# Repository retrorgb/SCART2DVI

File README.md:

# SCART2DVI
Please refer to the [SCART2DVI](https://www.retrorgb.com/scart2dvi.html) page on RetroRGB for more information.

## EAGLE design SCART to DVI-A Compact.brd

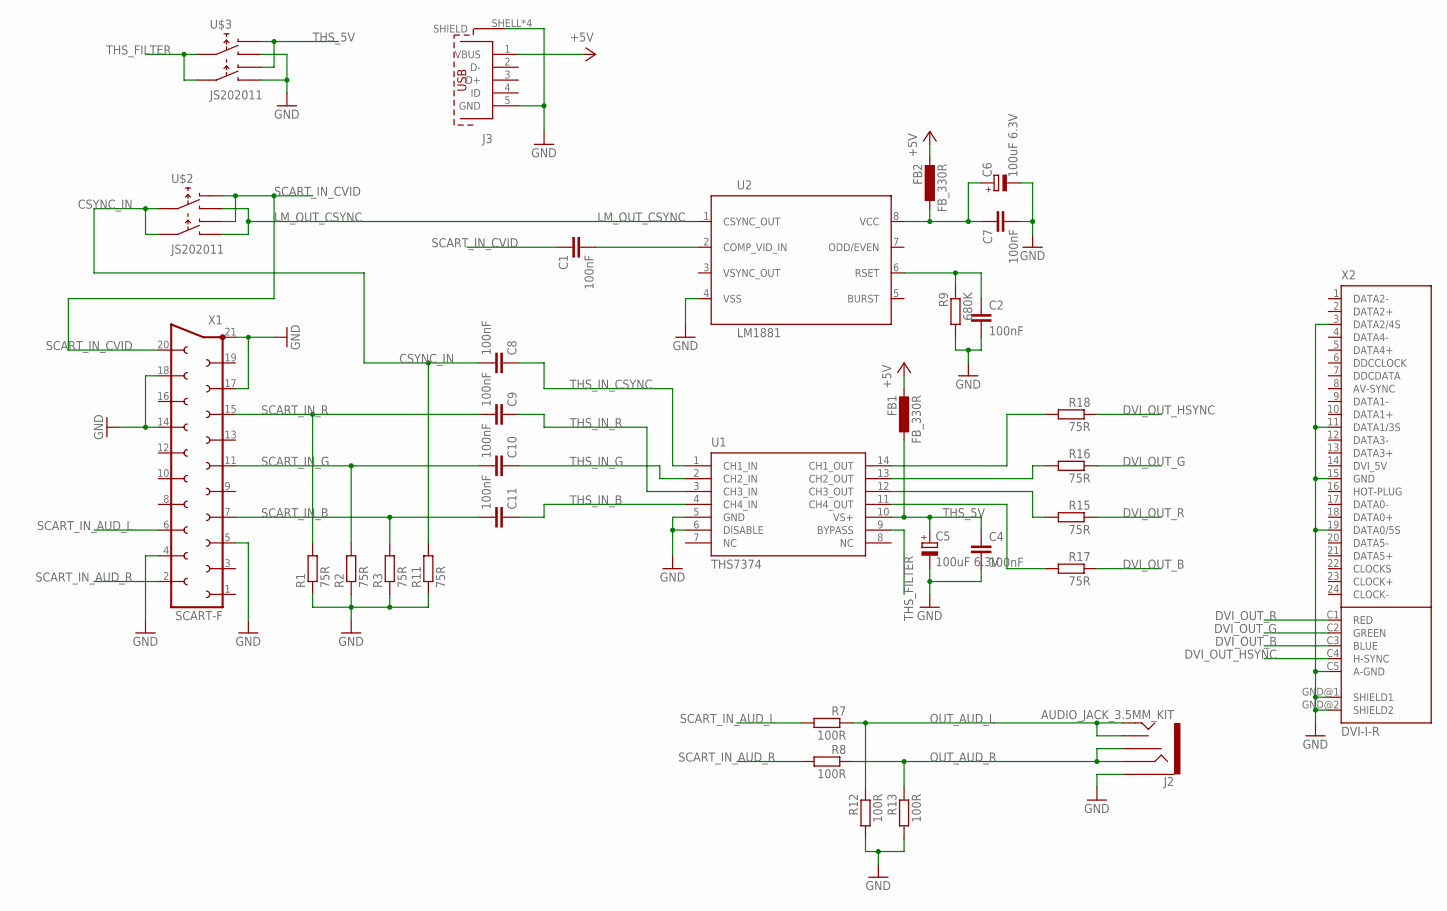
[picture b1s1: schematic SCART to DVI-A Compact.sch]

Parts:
C1, C2, C4, C7, C8, C9, C10, C11: 100nF; C0603
C5, C6: 100uF 6.3V; PANASONIC_B
FB1, FB2: FB_330R; L2012C
J2: AUDIO_JACK_3.5MM_KIT; AUDIO-JACK-KIT
J3: 629105150521
R1, R2, R3, R11, R15, R16, R17, R18: 75R; R0603
R7, R8, R12, R13: 100R; R0603
R9: 680K; R0603
U1: THS7374; SO14W
U2: LM1881; SO08
U$2, U$3: JS202011
X1: SCART-F
X2: DVI-I-R

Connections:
+5V: FB1.2, FB2.2, J3.1 (VBUS)
AGND: X2.C6 (AGND)
CH1_OUT: R15.2, U1.12 (CH3_OUT)
CH2_OUT: R16.2, U1.13 (CH2_OUT)
CH3_OUT: R17.2, U1.11 (CH4_OUT)
CH4_OUT: R18.2, U1.14 (CH1_OUT)
CSYNC_IN: C8.2, R11.2, U$2.2, U$2.5
DVI_5V: X2.14 (DVI_5V)
DVI_OUT_B: R17.1, X2.C3 (BLUE)
DVI_OUT_G: R16.1, X2.C2 (GREEN)
DVI_OUT_HSYNC: R18.1, X2.C4 (H-SYNC)
DVI_OUT_R: R15.1, X2.C1 (RED)
GND: C2.2, C4.2, C5.-, C6.-, C7.2, J2.SLEEVE, J3.5 (GND), J3.SHELL (SHIELD), J3.SHELL1 (SHIELD), J3.SHELL2 (SHIELD), J3.SHELL3 (SHIELD), R1.1, R2.1, R3.1, R9.2, R11.1, R12.2, R13.2, U1.5 (GND), U1.6 (DISABLE), U2.4 (VSS), U$3.1, U$3.4, X1.4, X1.5, X1.14, X1.17, X1.18, X1.21, X2.3 (DATA2/4S), X2.11 (DATA1/3S), X2.15 (GND), X2.19 (DATA0/5S), X2.C5 (A-GND), X2.GND@1 (SHIELD1), X2.GND@2 (SHIELD2)
LM_OUT_CSYNC: U2.1 (CSYNC_OUT), U$2.1, U$2.4
unnamed: C1.2, U2.2 (COMP_VID_IN)
unnamed: C6.+, C7.1, FB2.1, U2.8 (VCC)
unnamed: C2.1, R9.1, U2.6 (RSET)
OUT_AUD_L: J2.TIP, J2.TSH, R7.1, R12.1
OUT_AUD_R: J2.RING, J2.RSH, R8.1, R13.1
SCART_IN_AUD_L: R7.2, X1.6
SCART_IN_AUD_R: R8.2, X1.2
SCART_IN_B: C11.2, R3.2, X1.7
SCART_IN_CVID: C1.1, U$2.3, U$2.6, X1.20
SCART_IN_G: C10.2, R2.2, X1.11
SCART_IN_R: C9.2, R1.2, X1.15
THS_5V: C4.1, C5.+, FB1.1, U1.10 (VS+), U$3.3, U$3.6
THS_FILTER: U1.9 (BYPASS), U$3.2, U$3.5
THS_IN_B: C11.1, U1.4 (CH4_IN)
THS_IN_CSYNC: C8.1, U1.1 (CH1_IN)
THS_IN_G: C10.1, U1.2 (CH2_IN)
THS_IN_R: C9.1, U1.3 (CH3_IN)

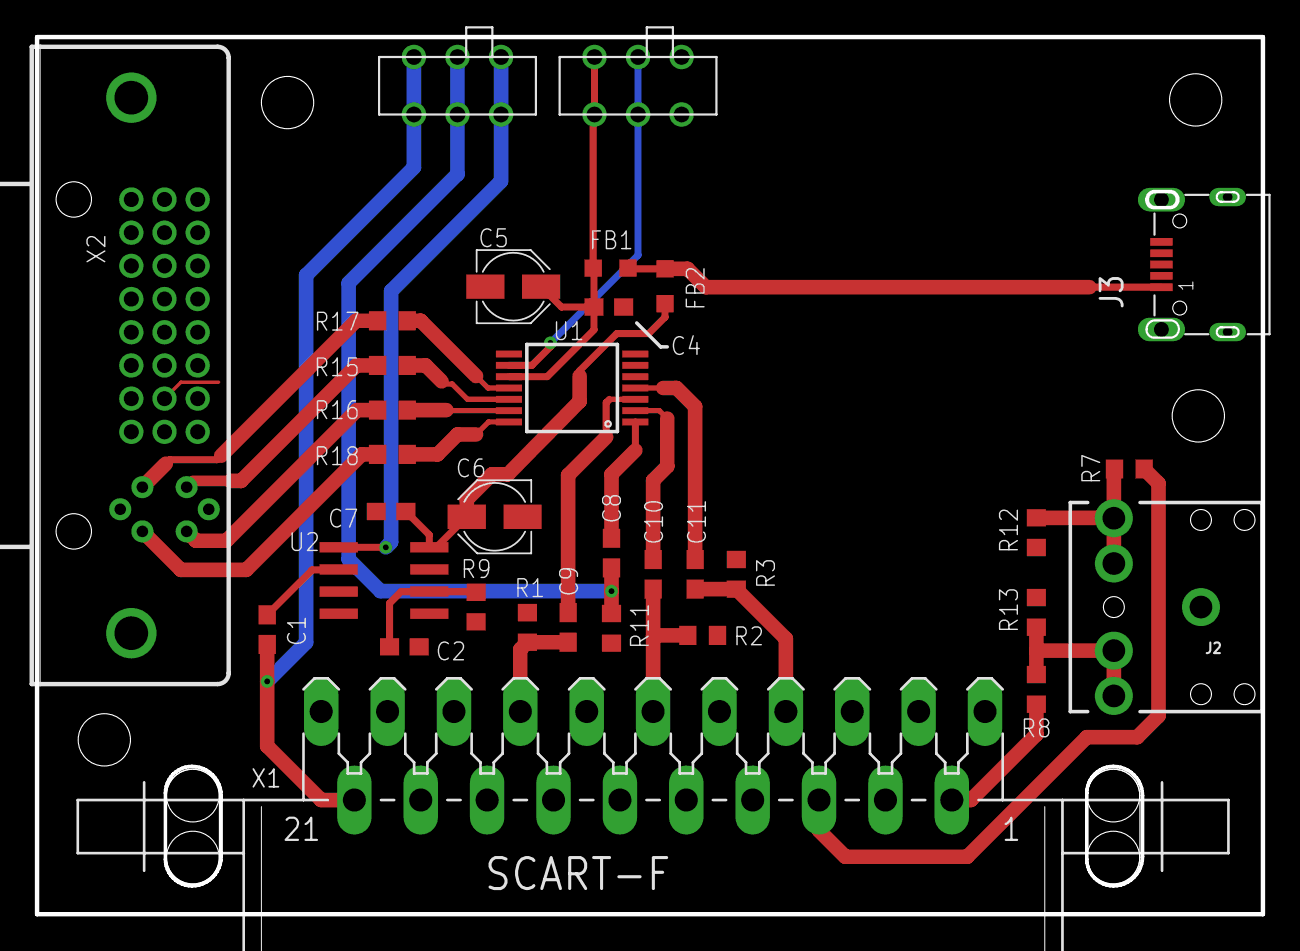
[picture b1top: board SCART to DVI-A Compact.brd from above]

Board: 2 copper layers, 70.4 x 50.3 mm, 33 parts (0 on the bottom side), 29 nets.

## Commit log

2019-06-13 Eagle Version
    Initial Eagle version of the board.
2019-06-13 KiCAD Version
    Converted to KiCAD
2019-06-13 Create license

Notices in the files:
parts and their libraries:
con-wurth: Copyright: Würth Elektronik
SparkFun-Connectors: Licensing: Creative Commons ShareAlike 4.0 International - https://creativecommons.org/licenses/by-sa/4.0
